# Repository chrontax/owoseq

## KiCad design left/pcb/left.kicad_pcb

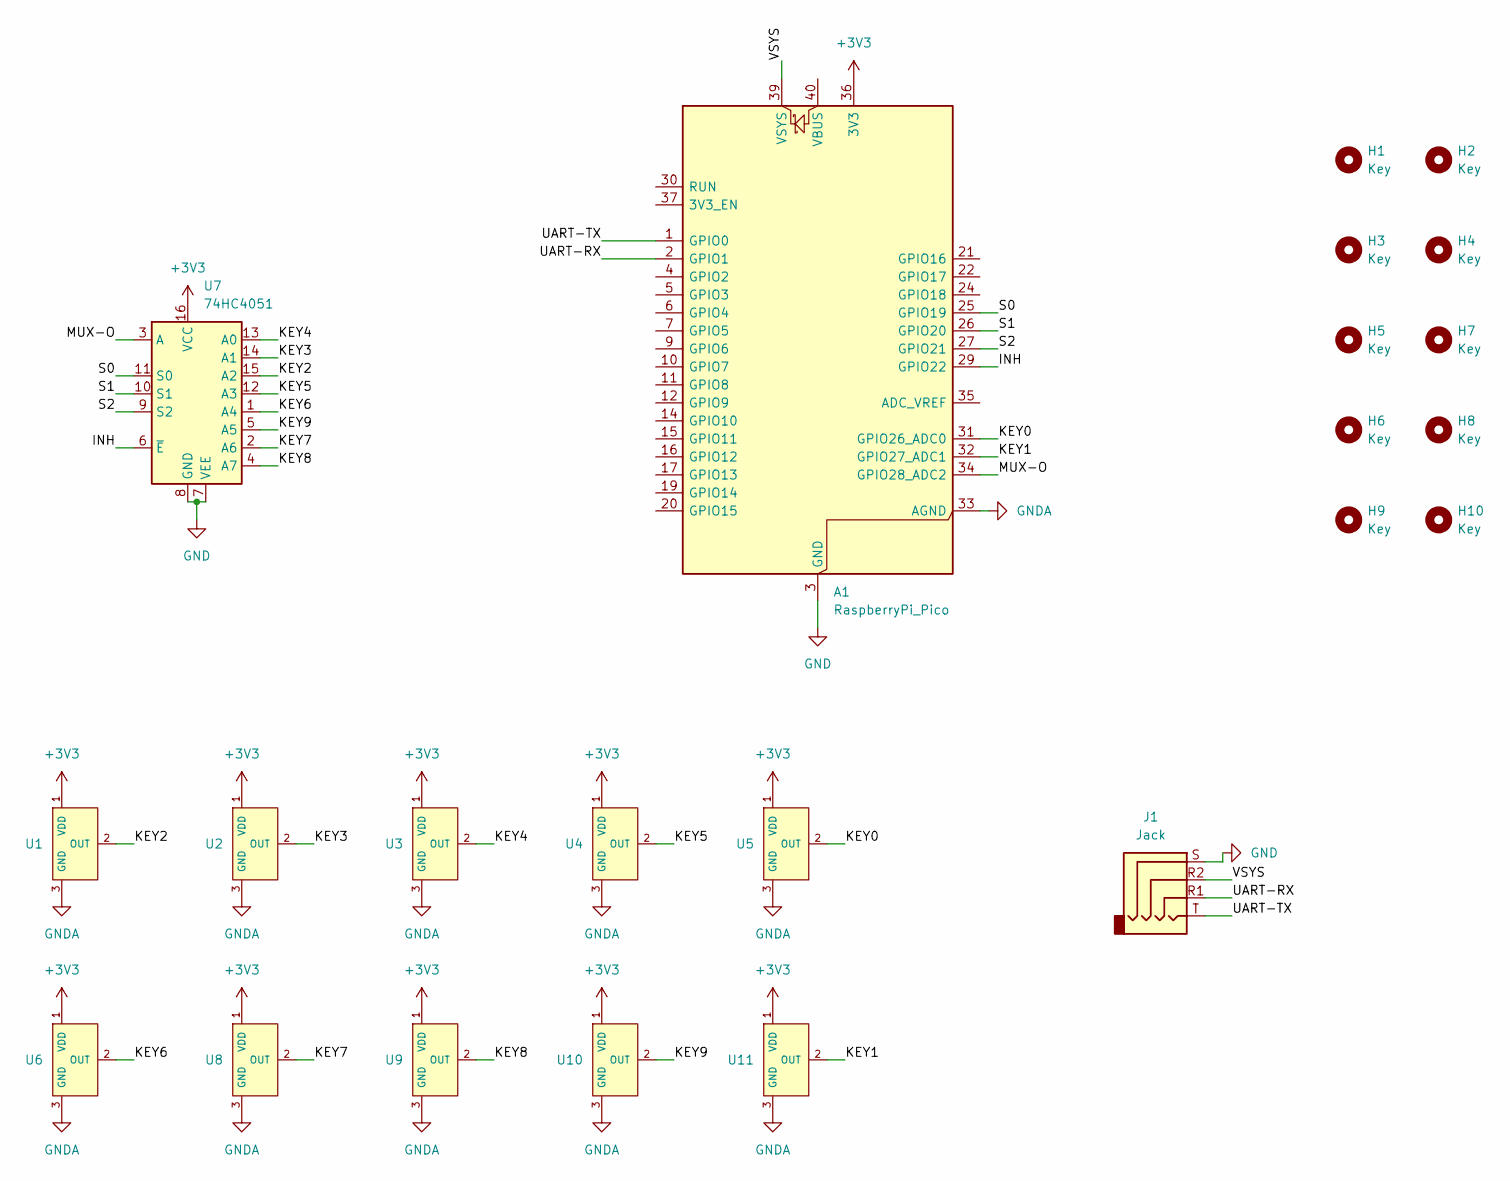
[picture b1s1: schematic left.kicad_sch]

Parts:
A1: RaspberryPi_Pico; RaspberryPi_Pico_Common_SMD
H1, H2, H3, H4, H5, H6, H7, H8, H9, H10: Key; MX-1U-NoPins
J1: Jack; Jack_3.5mm_PJ320D_Horizontal
U1, U2, U3, U4, U5, U6, U8, U9, U10, U11: Hall_Sensor; SOT-23; MPN GH39FKSW; LCSC Part C266230
U7: 74HC4051; SOIC-16W_5.3x10.2mm_P1.27mm

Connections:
+3V3: A1.36 (3V3), U1.1 (VDD), U2.1 (VDD), U3.1 (VDD), U4.1 (VDD), U5.1 (VDD), U6.1 (VDD), U7.16 (VCC), U8.1 (VDD), U9.1 (VDD), U10.1 (VDD), U11.1 (VDD)
/INH: A1.29 (GPIO22), U7.6 (~E)
/KEY0: A1.31 (GPIO26_ADC0), U5.2 (OUT)
/KEY1: A1.32 (GPIO27_ADC1), U11.2 (OUT)
/KEY2: U1.2 (OUT), U7.15 (A2)
/KEY3: U2.2 (OUT), U7.14 (A1)
/KEY4: U3.2 (OUT), U7.13 (A0)
/KEY5: U4.2 (OUT), U7.12 (A3)
/KEY6: U6.2 (OUT), U7.1 (A4)
/KEY7: U7.2 (A6), U8.2 (OUT)
/KEY8: U7.4 (A7), U9.2 (OUT)
/KEY9: U7.5 (A5), U10.2 (OUT)
/MUX-O: A1.34 (GPIO28_ADC2), U7.3 (A)
/S0: A1.25 (GPIO19), U7.11 (S0)
/S1: A1.26 (GPIO20), U7.10 (S1)
/S2: A1.27 (GPIO21), U7.9 (S2)
/UART-RX: A1.2 (GPIO1), J1.R1
/UART-TX: A1.1 (GPIO0), J1.T
/VSYS: A1.39 (VSYS), J1.R2
GND: A1.3 (GND), A1.8 (GND), A1.13 (GND), A1.18 (GND), A1.23 (GND), A1.28 (GND), A1.38 (GND), J1.S, U7.7 (VEE), U7.8 (GND)
GNDA: A1.33 (AGND), U1.3 (GND), U2.3 (GND), U3.3 (GND), U4.3 (GND), U5.3 (GND), U6.3 (GND), U8.3 (GND), U9.3 (GND), U10.3 (GND), U11.3 (GND)

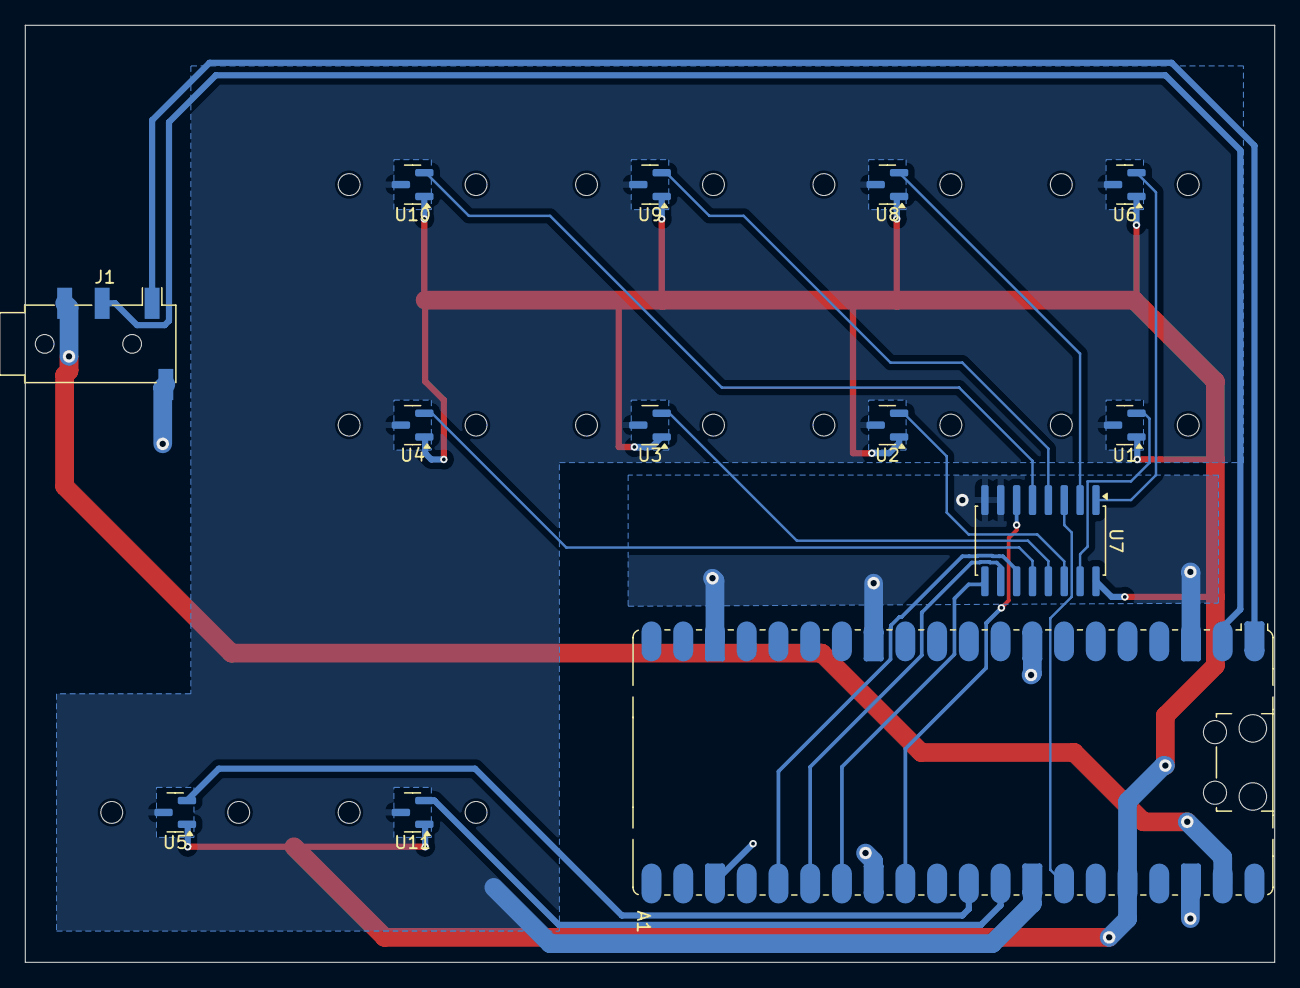
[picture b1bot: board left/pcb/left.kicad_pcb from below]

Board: 2 copper layers, 100.0 x 75.0 mm, 23 parts (13 on the bottom side), 21 nets.

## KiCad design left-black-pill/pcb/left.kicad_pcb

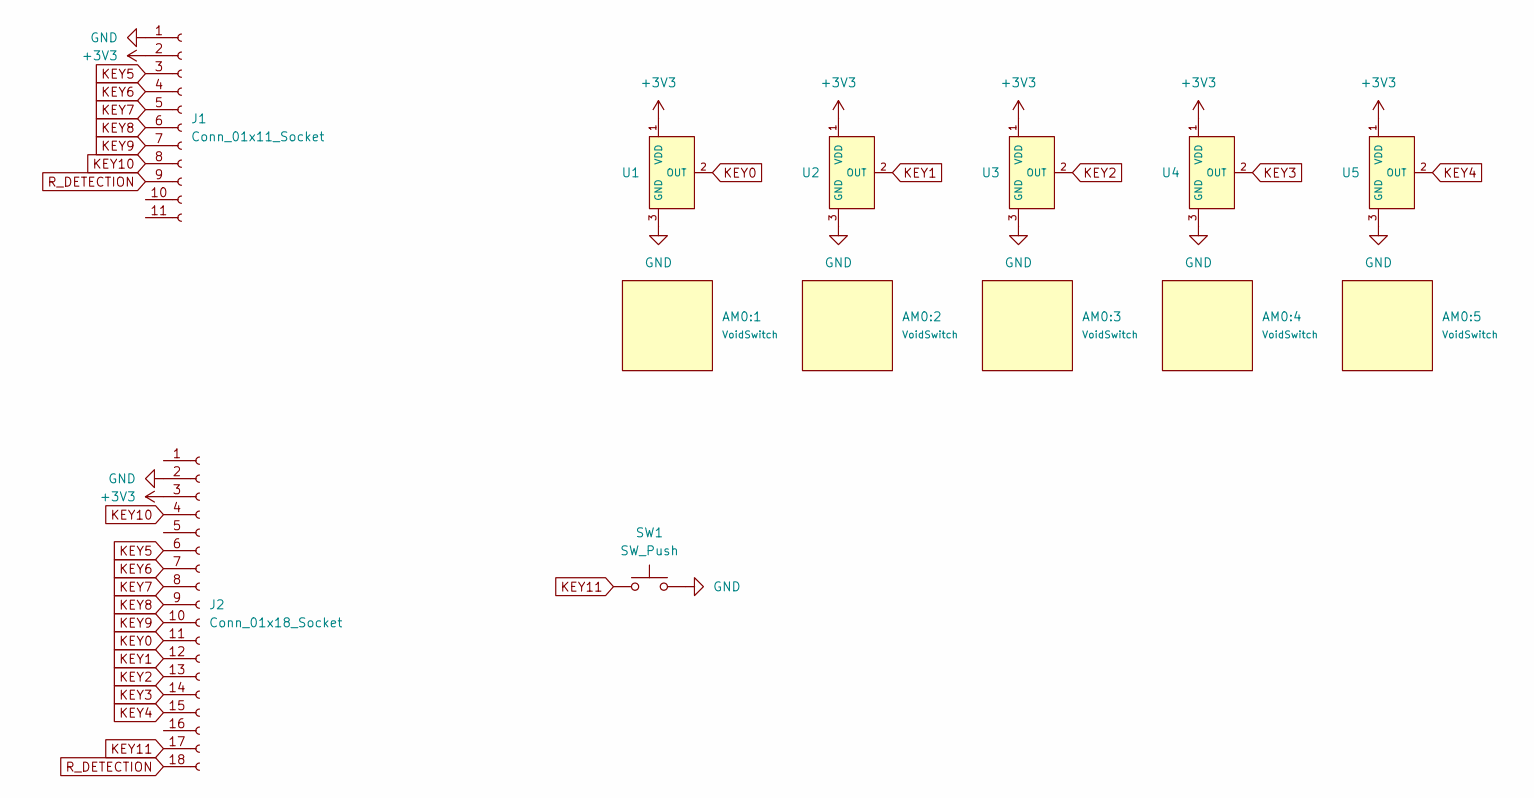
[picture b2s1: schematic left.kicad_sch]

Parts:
AM0:1, AM0:2, AM0:3, AM0:4, AM0:5: VoidSwitch; VoidSwitch_1u_SMD
J1: Conn_01x11_Socket; PinSocket_1x11_P2.54mm_Horizontal
J2: Conn_01x18_Socket; PinSocket_1x18_P2.54mm_Vertical
SW1: SW_Push; SW_Cherry_MX_1.00u_PCB
U1, U2, U3, U4, U5: Hall_Sensor; SOT-23; MPN GH39FKSW; LCSC Part C266230

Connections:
+3V3: J1.2, J2.3, U1.1 (VDD), U2.1 (VDD), U3.1 (VDD), U4.1 (VDD), U5.1 (VDD)
GND: J1.1, J2.2, SW1.2, U1.3 (GND), U2.3 (GND), U3.3 (GND), U4.3 (GND), U5.3 (GND)
KEY0: J2.11, U1.2 (OUT)
KEY1: J2.12, U2.2 (OUT)
KEY2: J2.13, U3.2 (OUT)
KEY3: J2.14, U4.2 (OUT)
KEY4: J2.15, U5.2 (OUT)
KEY5: J1.3, J2.6
KEY6: J1.4, J2.7
KEY7: J1.5, J2.8
KEY8: J1.6, J2.9
KEY9: J1.7, J2.10
KEY10: J1.8, J2.4
KEY11: J2.17, SW1.1
R_DETECTION: J1.9, J2.18

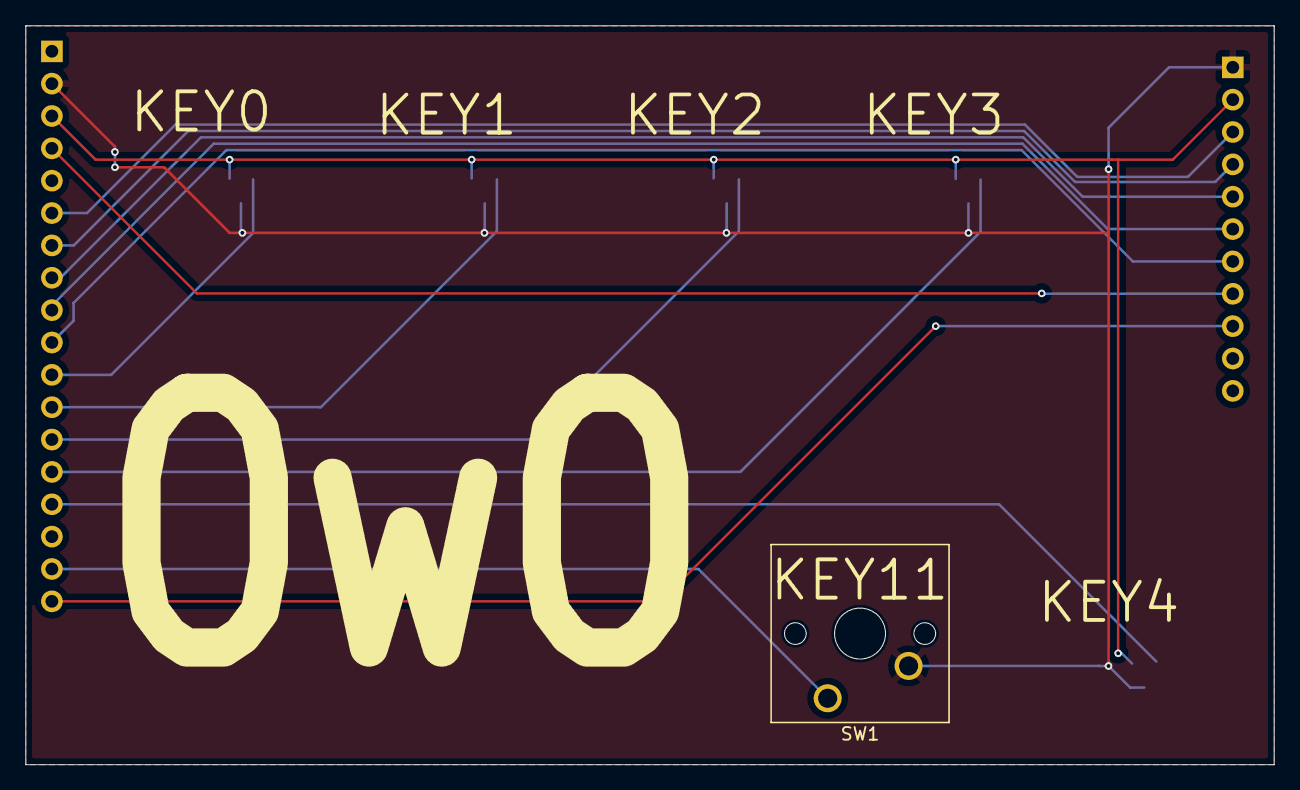
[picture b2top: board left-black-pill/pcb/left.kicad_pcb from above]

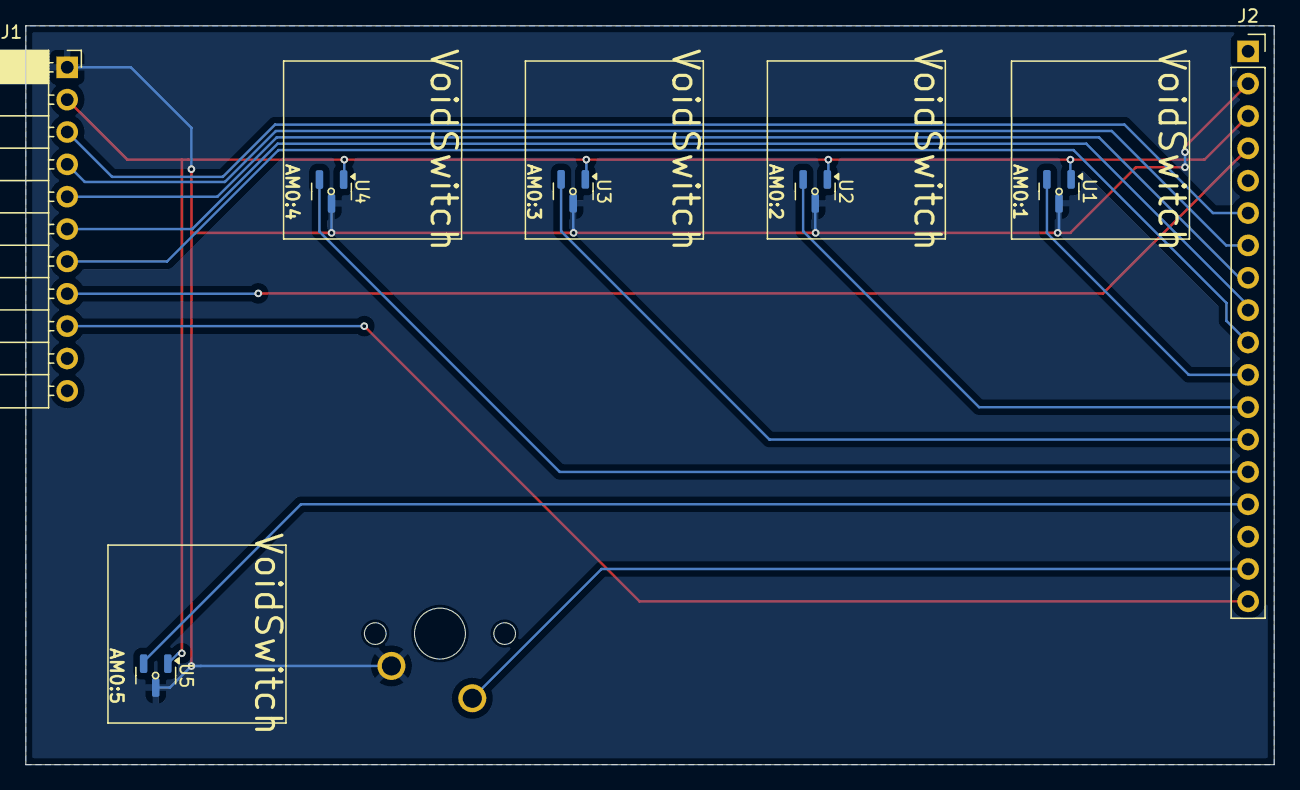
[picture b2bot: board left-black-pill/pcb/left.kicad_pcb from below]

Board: 2 copper layers, 98.0 x 58.0 mm, 13 parts (12 on the bottom side), 15 nets.

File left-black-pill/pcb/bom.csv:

Comment,Designator,Footprint,LCSC
Hall_Sensor,"U1,U2,U3,U4,U5",SOT-23,C266230
Conn_01x18_Socket,J2,PinSocket_1x18_P2.54mm_Vertical,C2905422
Conn_01x11_Socket,J1,PinSocket_1x11_P2.54mm_Horizontal,C2897393

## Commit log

2024-08-31 init
2024-09-01 case bottom
2024-09-01 case top part 1
2025-08-07 left pcb design
2025-08-08 add holes to fill and some rerouting
2025-08-12 initial case design
2025-08-12 add parameter for switch tolerance
2025-08-12 add FCBak files to gitignore
2025-08-12 fabrication output config
2025-09-03 case changes
2025-09-03 add usb prop hole
2025-09-03 move jack to the other side of the pcb
